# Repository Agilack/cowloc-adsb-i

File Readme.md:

Cowloc - ADS-B Receiver
=======================

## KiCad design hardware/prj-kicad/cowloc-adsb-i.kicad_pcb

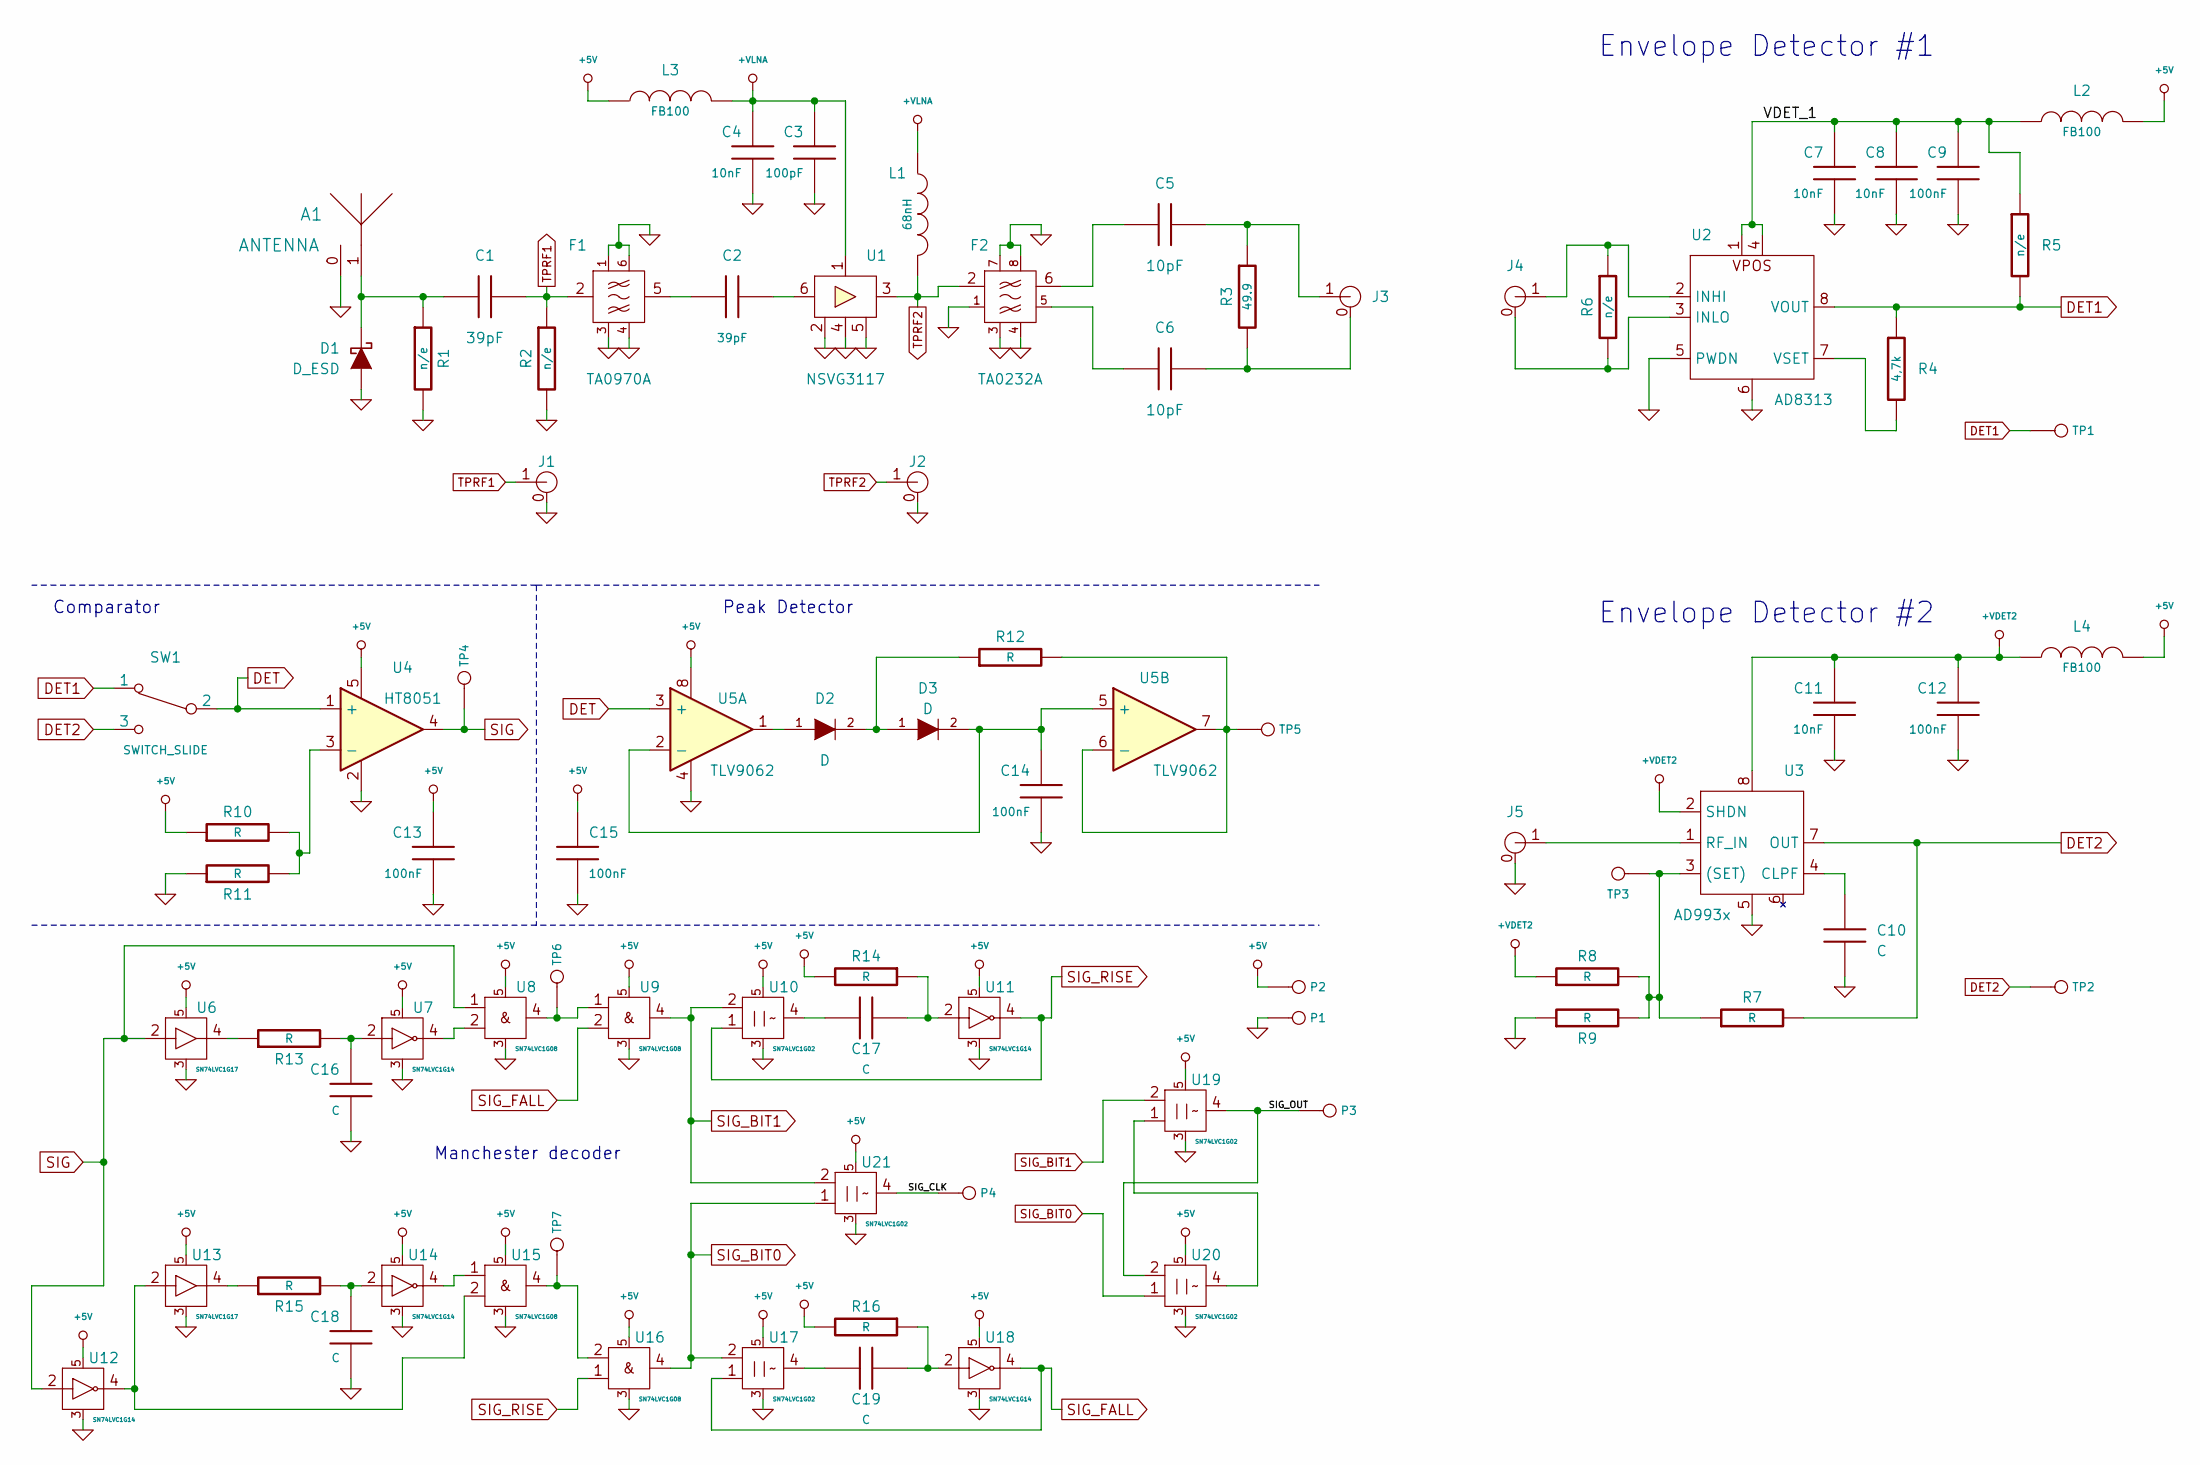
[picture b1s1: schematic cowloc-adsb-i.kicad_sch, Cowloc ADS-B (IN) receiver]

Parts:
A1: ANTENNA; CONN_SMA_RA
C1, C2: 39pF; SMD0603
C3: 100pF; SMD0603
C4, C7, C8, C11: 10nF; SMD0603
C5, C6: 10pF; SMD0603
C9, C12, C13, C14, C15: 100nF; SMD0603
C10, C16, C17, C18, C19: C; SMD0603
D1: D_ESD; SOD-123
D2, D3: D; SOD-123
F1: TA0970A; FLT_6
F2: TA0232A; FLT_3x8
J1, J2, J3, J4, J5: CONN_UFL-R-SMT-1
L1: 68nH; SMD0805
L2, L3, L4: FB100; SMD0603
P1, P2, P3, P4: CONN_1; TP_PIN
R1, R2, R5, R6: n/e; SMD0603
R3: 49.9; SMD0603
R4: 4,7k; SMD0603
R7, R8, R9, R10, R11, R12, R13, R14, R15, R16: R; SMD0603
SW1: SWITCH_SLIDE; SW_450301014042
TP1, TP2, TP3, TP4, TP5, TP6, TP7: CONN_1; TP_SMD
U1: NSVG3117; SC88
U2: AD8313; MSOP-8
U3: AD993x; MSOP-8
U4: HT8051; SOT23-5
U5: TLV9062; SOIC-8
U6, U13: SN74LVC1G17; SOT23-5
U7, U11, U12, U14, U18: SN74LVC1G14; SOT23-5
U8, U9, U15, U16: SN74LVC1G08; SOT23-5
U10, U17, U19, U20, U21: SN74LVC1G02; SOT23-5

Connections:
+5V: C13.1, C15.1, L2.2, L3.1, L4.2, P2.1, R10.1, R14.2, R16.2, U4.5, U5.8, U6.5, U7.5, U8.5, U9.5, U10.5, U11.5, U12.5, U13.5, U14.5, U15.5, U16.5, U17.5, U18.5, U19.5, U20.5, U21.5; also elsewhere on the board
+VDET2: C11.1, C12.1, L4.1, R8.1, U3.2 (SHDN), U3.8
+VLNA: C3.1, C4.1, L1.1, L3.2, U1.1
/SIG_CLK: P4.1, U21.4 (Y)
/SIG_OUT: P3.1, U19.4 (Y), U20.2 (A)
/VDET_1: C7.1, C8.1, C9.1, L2.1, R5.1, U2.1, U2.4
DET: SW1.2, U4.1 (+), U5.3 (+)
DET1: R4.1, R5.2, SW1.1, TP1.1, U2.8 (VOUT)
DET2: R7.2, SW1.3, TP2.1, U3.7 (OUT)
GND: A1.0, C3.2, C4.2, C7.2, C8.2, C9.2, C10.2, C11.2, C12.2, C13.2, C14.2, C15.2, C16.2, C18.2, D1.1 (A), F1.1, F1.3, F1.4, F1.6, F2.1, F2.3, F2.4, F2.7, F2.8, J1.0, J2.0, J5.0, P1.1, R1.2, R2.2, R9.1, R11.1, U1.2, U1.4, U1.5, U2.5 (PWDN), U2.6, U3.5, U4.2, U5.4, U6.3, U7.3, U8.3, U9.3, U10.3, U11.3, U12.3, U13.3, U14.3, U15.3, U16.3, U17.3, U18.3, U19.3, U20.3, U21.3; also elsewhere on the board
unnamed: C2.1, F1.5
unnamed: C2.2, U1.6
unnamed: C5.1, F2.6
unnamed: C5.2, J3.1, R3.1
unnamed: C6.1, F2.5
unnamed: C6.2, J3.0, R3.2
unnamed: A1.1, C1.1, D1.2 (K), R1.1
unnamed: D2.1 (A), U5.1
unnamed: D2.2 (K), D3.1 (A), R12.1
unnamed: C14.1, D3.2 (K), U5.2 (-), U5.5 (+)
unnamed: J4.1, R6.1, U2.2 (INHI)
unnamed: J4.0, R6.2, U2.3 (INLO)
unnamed: R4.2, U2.7 (VSET)
unnamed: R7.1, R8.2, R9.2, TP3.1, U3.3 ((SET))
unnamed: C10.1, U3.4 (CLPF)
unnamed: J5.1, U3.1 (RF_IN)
unnamed: R10.2, R11.2, U4.3 (-)
unnamed: R12.2, TP5.1, U5.6 (-), U5.7
unnamed: R13.1, U6.4 (Y)
unnamed: C16.1, R13.2, U7.2 (A)
unnamed: U7.4 (Y), U8.2 (A)
unnamed 31: TP6.1, U8.4 (Y), U9.1 (B); also elsewhere on the board
unnamed: C17.1, U10.4 (Y)
unnamed: C17.2, R14.1, U11.2 (A)
unnamed: U12.4 (Y), U13.2 (A), U15.2 (A)
unnamed: R15.1, U13.4 (Y)
unnamed: C18.1, R15.2, U14.2 (A)
unnamed: U14.4 (Y), U15.1 (B)
unnamed: TP7.1, U15.4 (Y), U16.2 (A)
unnamed: C19.1, U17.4 (Y)
unnamed: C19.2, R16.1, U18.2 (A)
unnamed: U19.1 (B), U20.4 (Y)
SIG: TP4.1, U4.4, U6.2 (A), U8.1 (B), U12.2 (A)
SIG_BIT0: U16.4 (Y), U17.2 (A), U20.1 (B), U21.1 (B)
SIG_BIT1: U9.4 (Y), U10.2 (A), U19.2 (A), U21.2 (A); also elsewhere on the board
SIG_FALL: U9.2 (A), U17.1 (B), U18.4 (Y); also elsewhere on the board
SIG_RISE: U10.1 (B), U11.4 (Y), U16.1 (B)
TPRF1: C1.2, F1.2, J1.1, R2.1
TPRF2: F2.2, J2.1, L1.2, U1.3

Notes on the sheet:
Envelope Detector #1
Envelope Detector #2
Manchester decoder
Comparator
Peak Detector

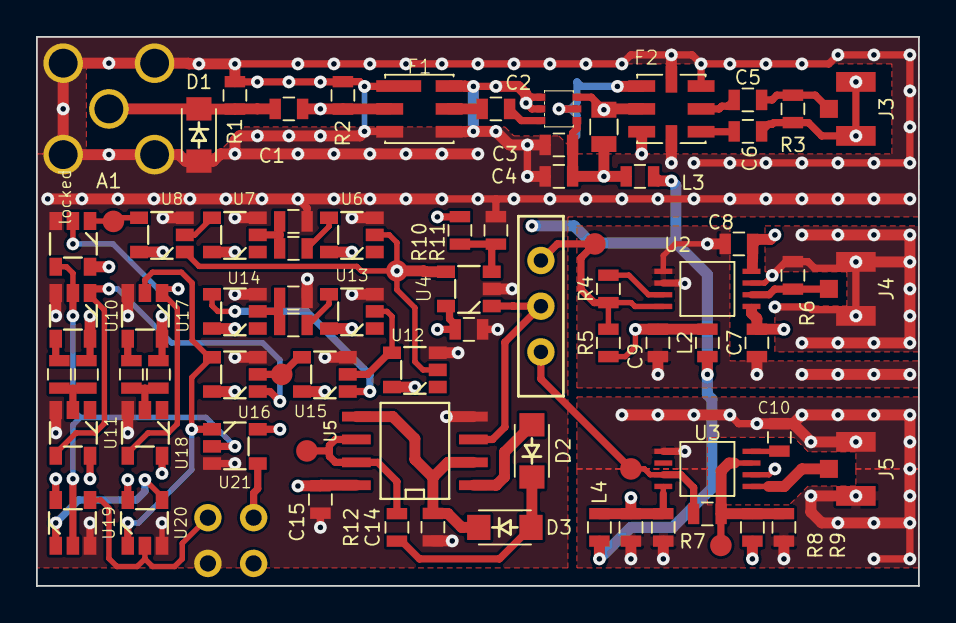
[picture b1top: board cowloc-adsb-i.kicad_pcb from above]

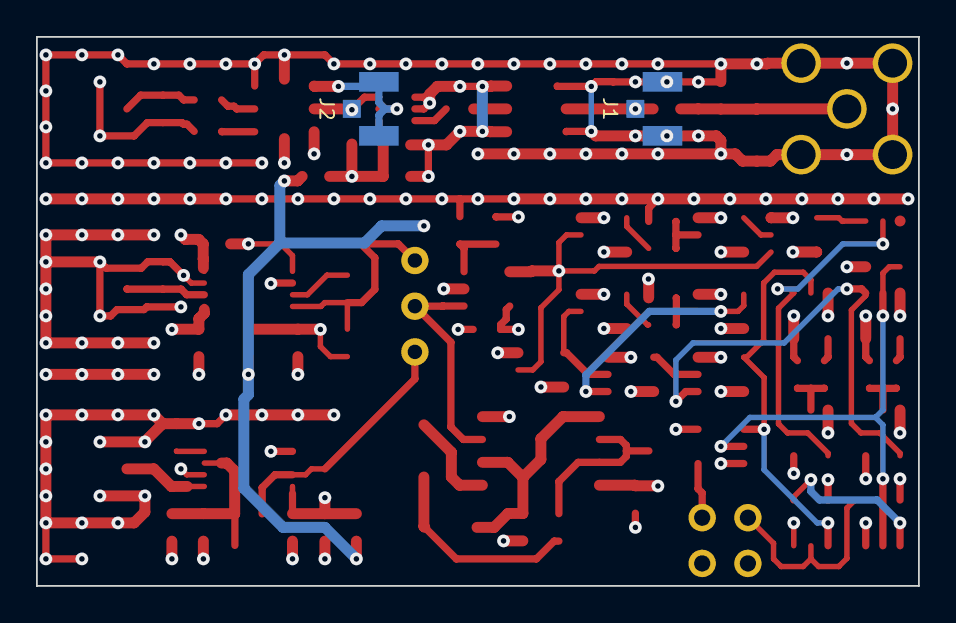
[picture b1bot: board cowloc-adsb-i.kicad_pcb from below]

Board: 4 copper layers, 49.0 x 30.5 mm, 83 parts (2 on the bottom side), 49 nets.

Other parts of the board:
locked: SN74LVC1G08; SOT23-5

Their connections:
+5V: locked.5; also elsewhere on the board
GND: locked.3; also elsewhere on the board
unnamed 31: locked.1 (B); also elsewhere on the board
SIG_BIT1: locked.4 (Y); also elsewhere on the board
SIG_FALL: locked.2 (A); also elsewhere on the board

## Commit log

2024-03-04 --=={ Create project }==--
2024-03-05 = ADD: Insert a first signal detector based on AD8313
2024-03-06 = ADD: Insert an alternate signal detector (AD993x) and a comparator on output
2024-03-07 = ADD: Insert an hard-wired signal decoder (beta!!)

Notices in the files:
hardware/prj-kicad/cowloc-adsb-i.kicad_pcb:
License: CC-by-SA
